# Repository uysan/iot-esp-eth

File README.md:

# ESP32 Ethernet, Wi-Fi & Serial Gateway

_Open Source Hardware Developed With Open Source Software_ [*](#development-software)

## Overview

<picture>
  <source media="(prefers-color-scheme: dark)" srcset="./pcb/3dviewb.png">
  <source media="(prefers-color-scheme: light)" srcset="./pcb/3dvieww.png">
  
</picture>

A hardware design which includes ESP32, Ethernet, Wi-Fi, USB and serial connectivity. **iot-esp-eth** is suitable to use as a gateway between Ethernet, Wi-Fi and serial. When used with [esp-at](https://github.com/espressif/esp-at) project, you can connect wired or wireless networks with AT commands sent to USB or serial ports. You may also operate it with custom firmware, since it is not different from a usual ESP32 development kit.

**iot-esp-eth** may be used as an attachment to a base board. Standalone usage with USB supply is possible as well.

ESP-IDF automatic bootloader activation is supported on USB port. This port is connected to UART0 of ESP32.

Schematic, PCB layout and antenna design are available in this repository. **iot-esp-eth** is compatible with many example projects at [espressif](https://github.com/espressif/) github repository.

## Table of Contents

- [PCB Design](./pcb/) : KiCAD project including schematic, layout, BOM, Gerber files.
- [Antenna Design](./antenna/) : OpenEMS project for PCB antenna design including simulation scripts, figures and prototype measurements.
- [Firmware](./firmware/) : espressif/esp-at project modified to include iot-esp-eth configuration.
- [Documents](./document/) : Project files for diagrams and documents.

## Pinout Diagram

## Block Diagram

## Datasheet

[UYS2101IA, UYS2101CA - ESP32 Ethernet, Wi-Fi & Serial Gateway](./document/uys2101.pdf)

## Features

- ESP32-D0WD-V3 Xtensa® Dual-core 32-bit LX6 240MHz MCU 
- 16 MB Serial Flash Memory
- 520 KB SRAM & 448 KB ROM
- 10/100 Mbit Ethernet (RTL8201F)
- Wi-Fi 802.11 b/g/n 2.4GHz
- Integrated 2.4GHz Antenna
- USB 2.0 Programming & Monitoring Interface
- 5V to 3.3V Voltage Regulator
- Supply Voltage Supervisor
- Built-in 40 MHz & 32.758 kHz MCU Crystals

## Development Software

This project was developed with open source tools including but not limited to KiCAD, OpenEMS, Octave, FreeCAD, Paraview, Inkscape and Scribus on a PC running Ubuntu Desktop edition.

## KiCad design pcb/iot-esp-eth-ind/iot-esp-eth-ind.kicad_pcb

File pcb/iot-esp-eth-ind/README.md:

# ESP32 Ethernet, Wi-Fi & Serial Gateway

_Open Source Hardware Developed With Open Source Software_ [*](#development-software)

## Overview

This directory contains KiCAD project files, generated PCB images, Gerber, panel configuration files, interactive HTML based assembly list, bill of materials and position (pick & place) data.

Components of the **iot-esp-eth-ind** board has an operating range of -40॰C to +85॰C. Board layout has 4-layers and is designed according to the JLCPCB impedance controlled stack up of [JLC04161H-7628](https://jlcpcb.com/impedance).

PCB panels can be automatically generated with KiKit (KiCAD plugin). Configuration files are in the related directory.

## Files

[Schematics](./iot-esp-eth-ind.pdf)

[PCB Layers](./iot-esp-eth-ind-layers.pdf)

[Bill of Materials](./iot-esp-eth-ind-bom.csv)

[Position Data](./iot-esp-eth-ind-all-pos.csv)

[Interactive assembly part list](./bom/ibom.html)

[Panel Configuration](./panel/config.json)

[Dimensions](./iot-esp-eth-ind-dimensions.pdf)

## Images

Copper layers:

Top view:

Bottom view:

## Development Software

This project was developed with open source tools including but not limited to KiCAD, OpenEMS, Octave, FreeCAD, Paraview, Inkscape and Scribus on a PC running Ubuntu Desktop edition.

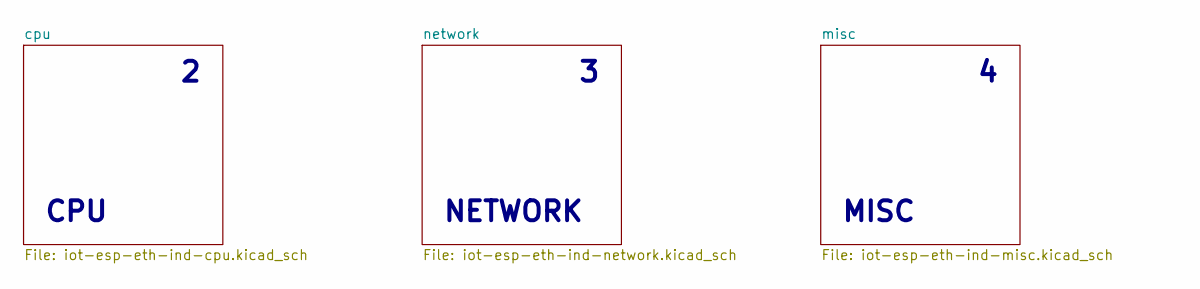
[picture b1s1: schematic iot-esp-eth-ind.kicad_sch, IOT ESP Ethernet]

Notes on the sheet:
NETWORK
MISC
CPU

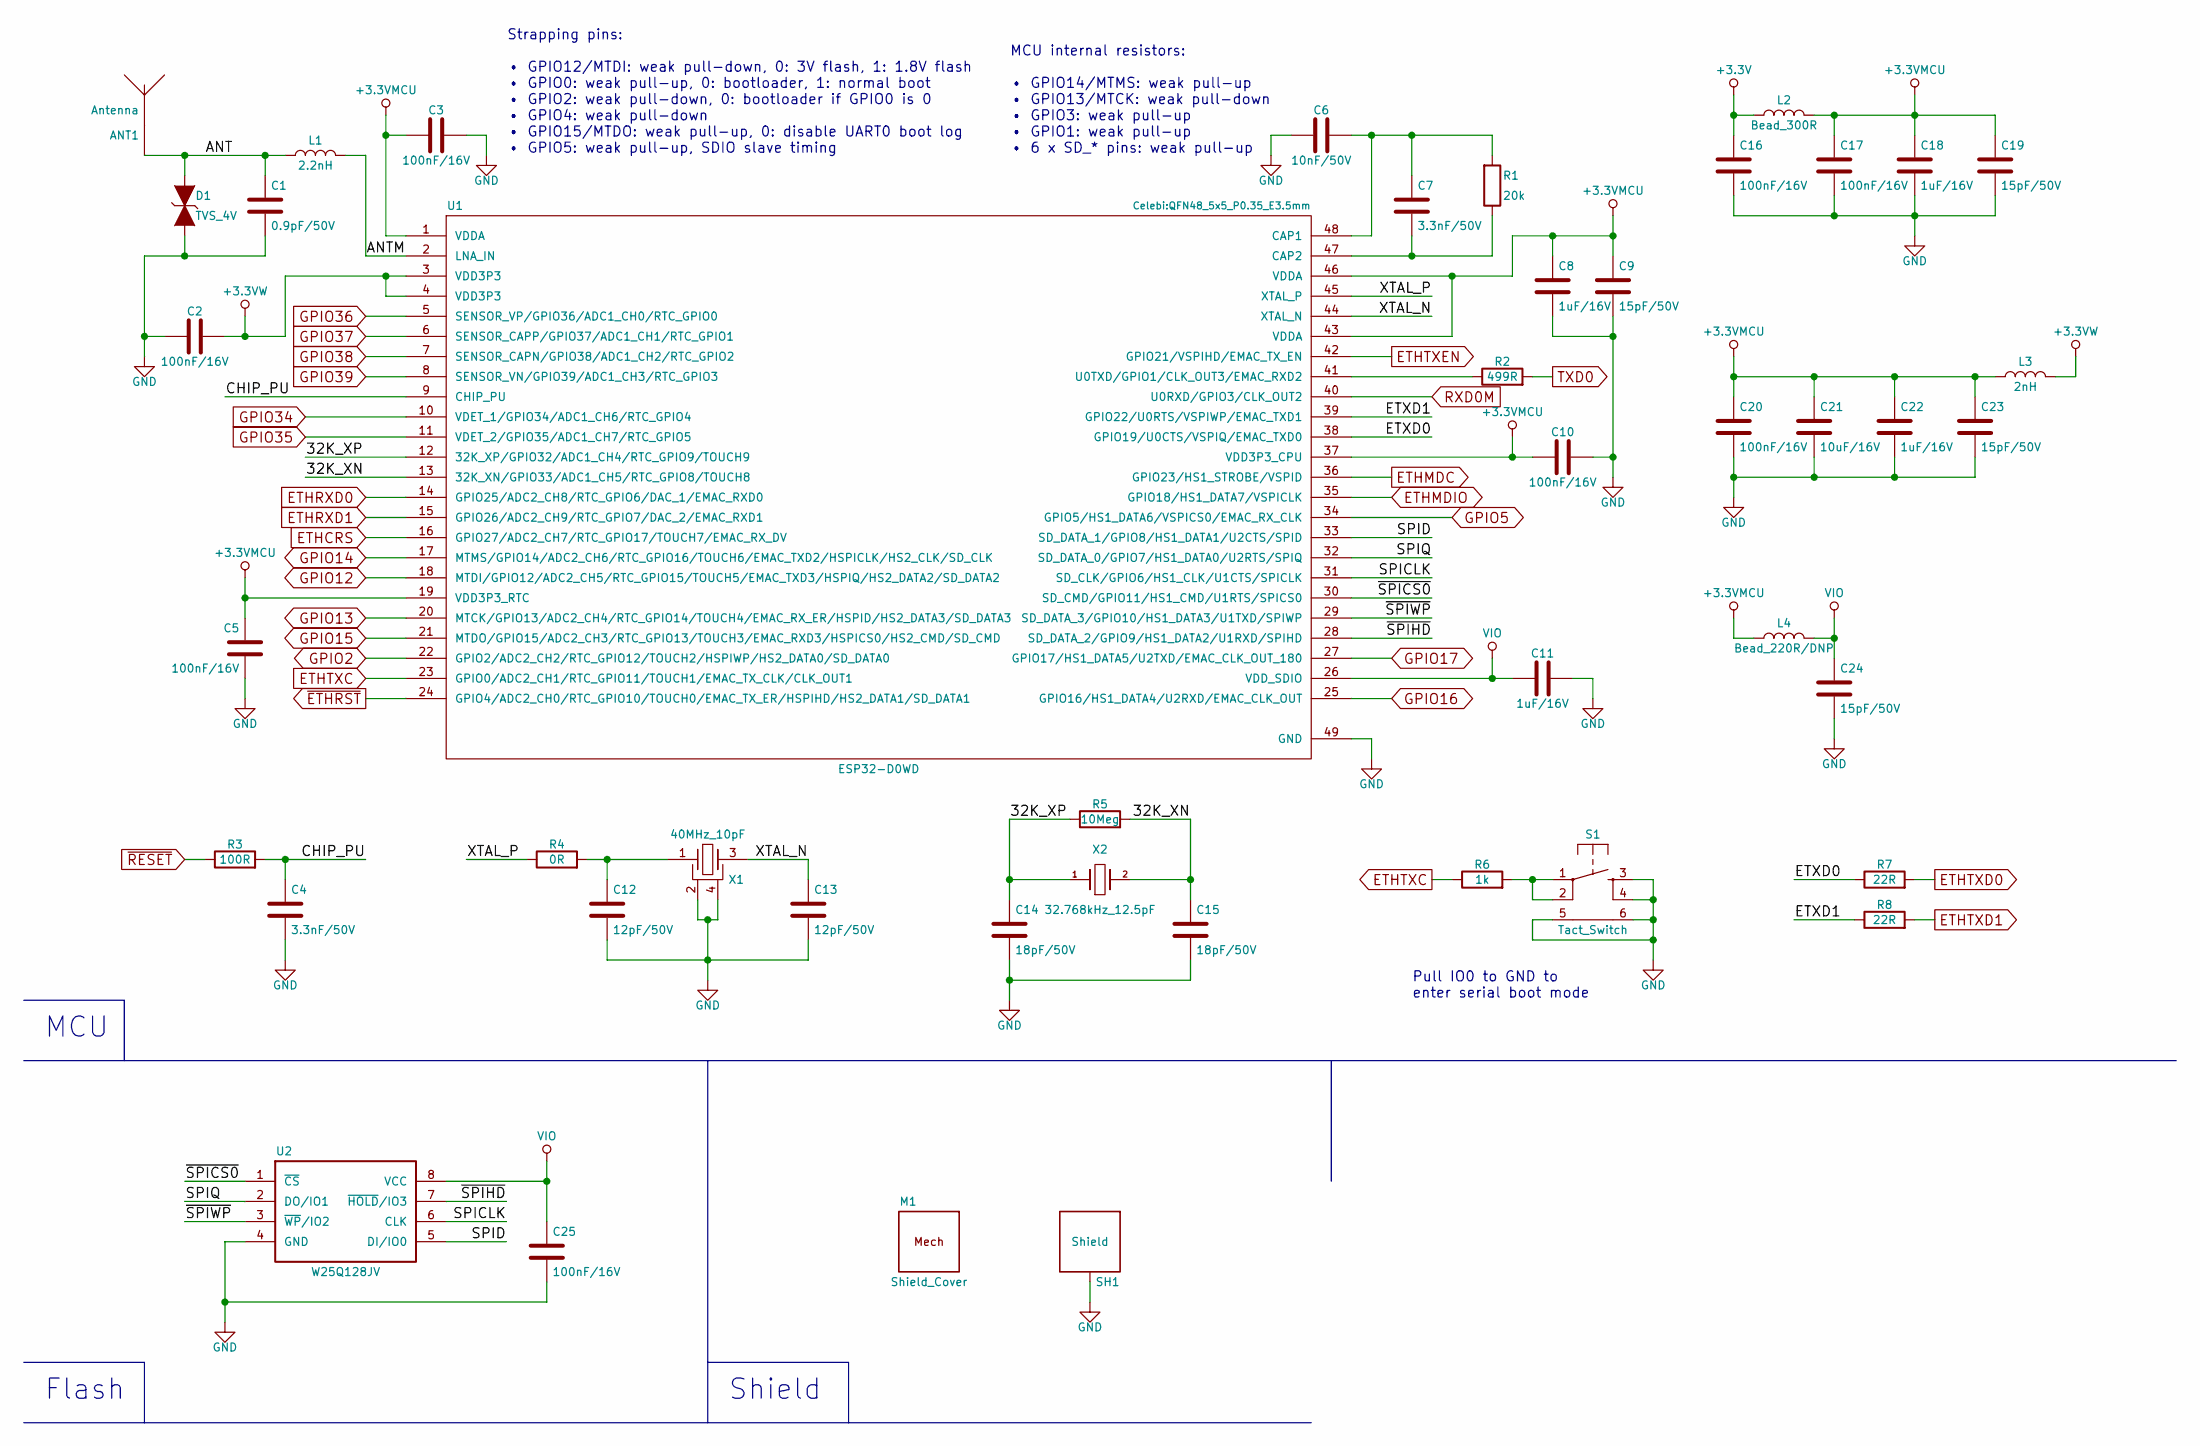
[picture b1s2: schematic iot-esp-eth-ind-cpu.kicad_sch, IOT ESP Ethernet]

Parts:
ANT1: Antenna; N.A.; Tolerance _; PartNumber _; Digikey _
C1: 0.9pF/50V; SM0402C; Tolerance 0.1pF; PartNumber 885392005022; Digikey !13-CC0402BRNPO9BNR90CT-ND
C2, C3, C5, C10, C16, C17, C20, C25: 100nF/16V; SM0402C; Tolerance 10%; PartNumber CL05B104KO5NNNC; Digikey 1276-1001-1-ND
C4, C7: 3.3nF/50V; SM0402C; Tolerance 10%; PartNumber CL05B332KB5NNNC; Digikey 1276-1552-1-ND
C6: 10nF/50V; SM0402C; Tolerance 10%; PartNumber CC0402KRX7R9BB103; Digikey 311-1349-1-ND
C8, C11, C18, C22: 1uF/16V; SM0603C; Tolerance 10%; PartNumber CC0603KRX7R7BB105; Digikey 311-1446-1-ND
C9, C19, C23, C24: 15pF/50V; SM0402C; Tolerance 5%; PartNumber CC0402JRNPO9BN150; Digikey 311-1017-1-ND
C12, C13: 12pF/50V; SM0402C; Tolerance 5%; PartNumber CC0402JRNPO9BN120; Digikey 311-1016-1-ND
C14, C15: 18pF/50V; SM0402C; Tolerance 5%; PartNumber CC0402JRNPO9BN180; Digikey 311-1415-1-ND
C21: 10uF/16V; SM0805C; Tolerance 10%; PartNumber CL21B106KOQNNNE; Digikey 1276-2872-1-ND
D1: TVS_4V; SM0402V; Tolerance _; PartNumber LXES15AAA1-153; Digikey 490-13210-2-ND
L1: 2.2nH; SM0402L; Tolerance 0.1nH; PartNumber 7447840022G; Digikey 732-7447840022GCT-ND
L2: Bead_300R; SM0603L; Tolerance 25%; PartNumber 742792641; Digikey 732-1592-1-ND
L3: 2nH; SM0402L; Tolerance 0.2nH; PartNumber 744765020A; Digikey 732-1705-1-ND
L4: Bead_220R/DNP; SM0402L; Tolerance 25%; PartNumber 742792780; Digikey 732-1569-1-ND
M1: Shield_Cover; N.A.; Tolerance _; PartNumber 36003160S; Digikey 732-11644-1-ND
R1: 20k; SM0402; Tolerance 1%; PartNumber RC0402FR-0720KL; Digikey 311-20.0KLRCT-ND
R2: 499R; SM0402; Tolerance 1%; PartNumber RC0402FR-07499RL; Digikey 311-499LRCT-ND
R3: 100R; SM0402; Tolerance 1%; PartNumber RC0402FR-07100RL; Digikey 311-100LRCT-ND
R4: 0R; SM0402; Tolerance Jumper; PartNumber RC0402JR-070RL; Digikey 311-0.0JRCT-ND
R5: 10Meg; SM0402; Tolerance 1%; PartNumber RC0402FR-0710ML; Digikey 311-10.0MLRCT-ND
R6: 1k; SM0402; Tolerance 1%; PartNumber RC0402FR-071KL; Digikey 311-1.00KLRCT-ND
R7, R8: 22R; SM0402; Tolerance 1%; PartNumber RC0402FR-0722RL; Digikey 311-22.0LRCT-ND
S1: Tact_Switch; switch-WE-WS-TASV-3x2.6_H1.4mm; Tolerance _; PartNumber 435171014816; Digikey 732-435171014816CT-ND
SH1: Shield; shield-36103166S; Tolerance _; PartNumber 36103166S; Digikey 732-11652-1-ND
U1: ESP32-D0WD; QFN48_5x5_P0.35_E3.5mm; Tolerance _; PartNumber ESP32-D0WD-V3; Digikey 1904-ESP32-D0WD-V3CT-ND
U2: W25Q128JV; SO8_5.2x5.2_P1.27mm; Tolerance _; PartNumber W25Q128JVSIQ; Digikey W25Q128JVSIQ-ND
X1: 40MHz_10pF; xtal-2.5x2.0mm_4pin; Tolerance 10ppm; PartNumber R2520-40.000-10-F-1010-EXT-TR; Digikey 2151-R2520-40.000-10-F-1010-EXT-TRCT-ND
X2: 32.768kHz_12.5pF; xtal-3.2x1.5mm; Tolerance 10ppm; PartNumber RT3215-32.768-12.5-TR-10PPM; Digikey 2151-RT3215-32.768-12.5-TR-10PPMCT-ND

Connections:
+3.3V: C16.1, L2.1; also elsewhere on the board
+3.3VMCU: C3.2, C5.1, C8.1, C9.1, C10.2, C17.1, C18.1, C19.1, C20.1, C21.1, C22.1, C23.1, L2.2, L3.1, L4.1, U1.1 (VDDA), U1.19 (VDD3P3_RTC), U1.37 (VDD3P3_CPU), U1.43 (VDDA), U1.46 (VDDA)
+3.3VW: C2.1, L3.2, U1.3 (VDD3P3), U1.4 (VDD3P3)
/cpu/32K_XN: C15.1, R5.2, U1.13 (32K_XN/GPIO33/ADC1_CH5/RTC_GPIO8/TOUCH8), X2.2 (B)
/cpu/32K_XP: C14.1, R5.1, U1.12 (32K_XP/GPIO32/ADC1_CH4/RTC_GPIO9/TOUCH9), X2.1 (A)
/cpu/ANT: ANT1.1, C1.1, D1.2 (A), L1.1
/cpu/ANTM: L1.2, U1.2 (LNA_IN)
/cpu/CHIP_PU: C4.1, R3.2, U1.9 (CHIP_PU)
/cpu/ETXD0: R7.1, U1.38 (GPIO19/U0CTS/VSPIQ/EMAC_TXD0)
/cpu/ETXD1: R8.1, U1.39 (GPIO22/U0RTS/VSPIWP/EMAC_TXD1)
/cpu/SPICLK: U1.31 (SD_CLK/GPIO6/HS1_CLK/U1CTS/SPICLK), U2.6 (CLK)
/cpu/SPID: U1.33 (SD_DATA_1/GPIO8/HS1_DATA1/U2CTS/SPID), U2.5 (DI/IO0)
/cpu/SPIQ: U1.32 (SD_DATA_0/GPIO7/HS1_DATA0/U2RTS/SPIQ), U2.2 (DO/IO1)
/cpu/XTAL_N: C13.1, U1.44 (XTAL_N), X1.3 (B)
/cpu/XTAL_P: R4.1, U1.45 (XTAL_P)
/cpu/~SPICS0: U1.30 (SD_CMD/GPIO11/HS1_CMD/U1RTS/SPICS0), U2.1 (~CS)
/cpu/~SPIHD: U1.28 (SD_DATA_2/GPIO9/HS1_DATA2/U1RXD/SPIHD), U2.7 (~HOLD/IO3)
/cpu/~SPIWP: U1.29 (SD_DATA_3/GPIO10/HS1_DATA3/U1TXD/SPIWP), U2.3 (~WP/IO2)
ETHCRS: U1.16 (GPIO27/ADC2_CH7/RTC_GPIO17/TOUCH7/EMAC_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); also elsewhere on the board
ETHMDC: U1.36 (GPIO23/HS1_STROBE/VSPID); also elsewhere on the board
ETHMDIO: U1.35 (GPIO18/HS1_DATA7/VSPICLK); also elsewhere on the board
ETHRXD0: U1.14 (GPIO25/ADC2_CH8/RTC_GPIO6/DAC_1/EMAC_RX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); also elsewhere on the board
ETHRXD1: U1.15 (GPIO26/ADC2_CH9/RTC_GPIO7/DAC_2/EMAC_RX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); also elsewhere on the board
ETHTXC: R6.1, U1.23 (GPIO0/ADC2_CH1/RTC_GPIO11/TOUCH1/EMAC_T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); also elsewhere on the board
ETHTXD0: R7.2; also elsewhere on the board
ETHTXD1: R8.2; also elsewhere on the board
ETHTXEN: U1.42 (GPIO21/VSPIHD/EMAC_TX_EN); also elsewhere on the board
GND: C1.2, C2.2, C3.1, C4.2, C5.2, C6.1, C8.2, C9.2, C10.1, C11.2, C12.2, C13.2, C14.2, C15.2, C16.2, C17.2, C18.2, C19.2, C20.2, C21.2, C22.2, C23.2, C24.2, C25.2, D1.1 (A), S1.3, S1.4, S1.5, S1.6, SH1.1 (GND), U1.49 (GND), U2.4 (GND), X1.2 (GND), X1.4 (GND); also elsewhere on the board
GPIO2: U1.22 (GPIO2/ADC2_CH2/RTC_GPIO12/TOUCH2/HSPIWP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); also elsewhere on the board
GPIO5: U1.34 (GPIO5/HS1_DATA6/VSPICS0/EMAC_RX_CLK); also elsewhere on the board
GPIO12: U1.18 (MTDI/GPIO12/ADC2_CH5/RTC_GPIO15/TOUCH5/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); also elsewhere on the board
GPIO13: U1.20 (MTCK/GPIO13/ADC2_CH4/RTC_GPIO14/TOUCH4/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); also elsewhere on the board
GPIO14: U1.17 (MTMS/GPIO14/ADC2_CH6/RTC_GPIO16/TOUCH6/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); also elsewhere on the board
GPIO15: U1.21 (MTDO/GPIO15/ADC2_CH3/RTC_GPIO13/TOUCH3/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); also elsewhere on the board
GPIO16: U1.25 (GPIO16/HS1_DATA4/U2RXD/EMAC_CLK_OUT); also elsewhere on the board
GPIO17: U1.27 (GPIO17/HS1_DATA5/U2TXD/EMAC_CLK_OUT_180); also elsewhere on the board
GPIO34: U1.10 (VDET_1/GPIO34/ADC1_CH6/RTC_GPIO4); also elsewhere on the board
GPIO35: U1.11 (VDET_2/GPIO35/ADC1_CH7/RTC_GPIO5); also elsewhere on the board
GPIO36: U1.5 (SENSOR_VP/GPIO36/ADC1_CH0/RTC_GPIO0); also elsewhere on the board
GPIO37: U1.6 (SENSOR_CAPP/GPIO37/ADC1_CH1/RTC_GPIO1); also elsewhere on the board
GPIO38: U1.7 (SENSOR_CAPN/GPIO38/ADC1_CH2/RTC_GPIO2); also elsewhere on the board
GPIO39: U1.8 (SENSOR_VN/GPIO39/ADC1_CH3/RTC_GPIO3); also elsewhere on the board
unnamed: C6.2, C7.1, R1.2, U1.48 (CAP1)
unnamed: C7.2, R1.1, U1.47 (CAP2)
unnamed: C12.1, R4.2, X1.1 (A)
unnamed: R2.1, U1.41 (U0TXD/GPIO1/CLK_OUT3/EMAC_RXD2)
unnamed: R6.2, S1.1, S1.2
RXD0M: U1.40 (U0RXD/GPIO3/CLK_OUT2); also elsewhere on the board
TXD0: R2.2; also elsewhere on the board
VIO: C11.1, C24.1, C25.1, L4.2, U1.26 (VDD_SDIO), U2.8 (VCC)
~ETHRST: U1.24 (GPIO4/ADC2_CH0/RTC_GPIO10/TOUCH0/EMAC_T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); also elsewhere on the board
~RESET: R3.1; also elsewhere on the board

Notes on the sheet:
MCU internal resistors: • GPIO14/MTMS: weak pull-up • GPIO13/MTCK: weak pull-down • GPIO3: weak pull-up • GPIO1: weak pull-up • 6 x SD_* pins: weak pull-up
Shield
Flash
MCU
Strapping pins: • GPIO12/MTDI: weak pull-down, 0: 3V flash, 1: 1.8V flash • GPIO0: weak pull-up, 0: bootloader, 1: normal boot • GPIO2: weak pull-down, 0: bootloader if GPIO0 is 0 • GPIO4: weak pull-down • GPIO15/MTDO: weak pull-up, 0: disable UART0 boot log • GPIO5: weak pull-up, SDIO slave timing
Pull IO0 to GND to enter serial boot mode

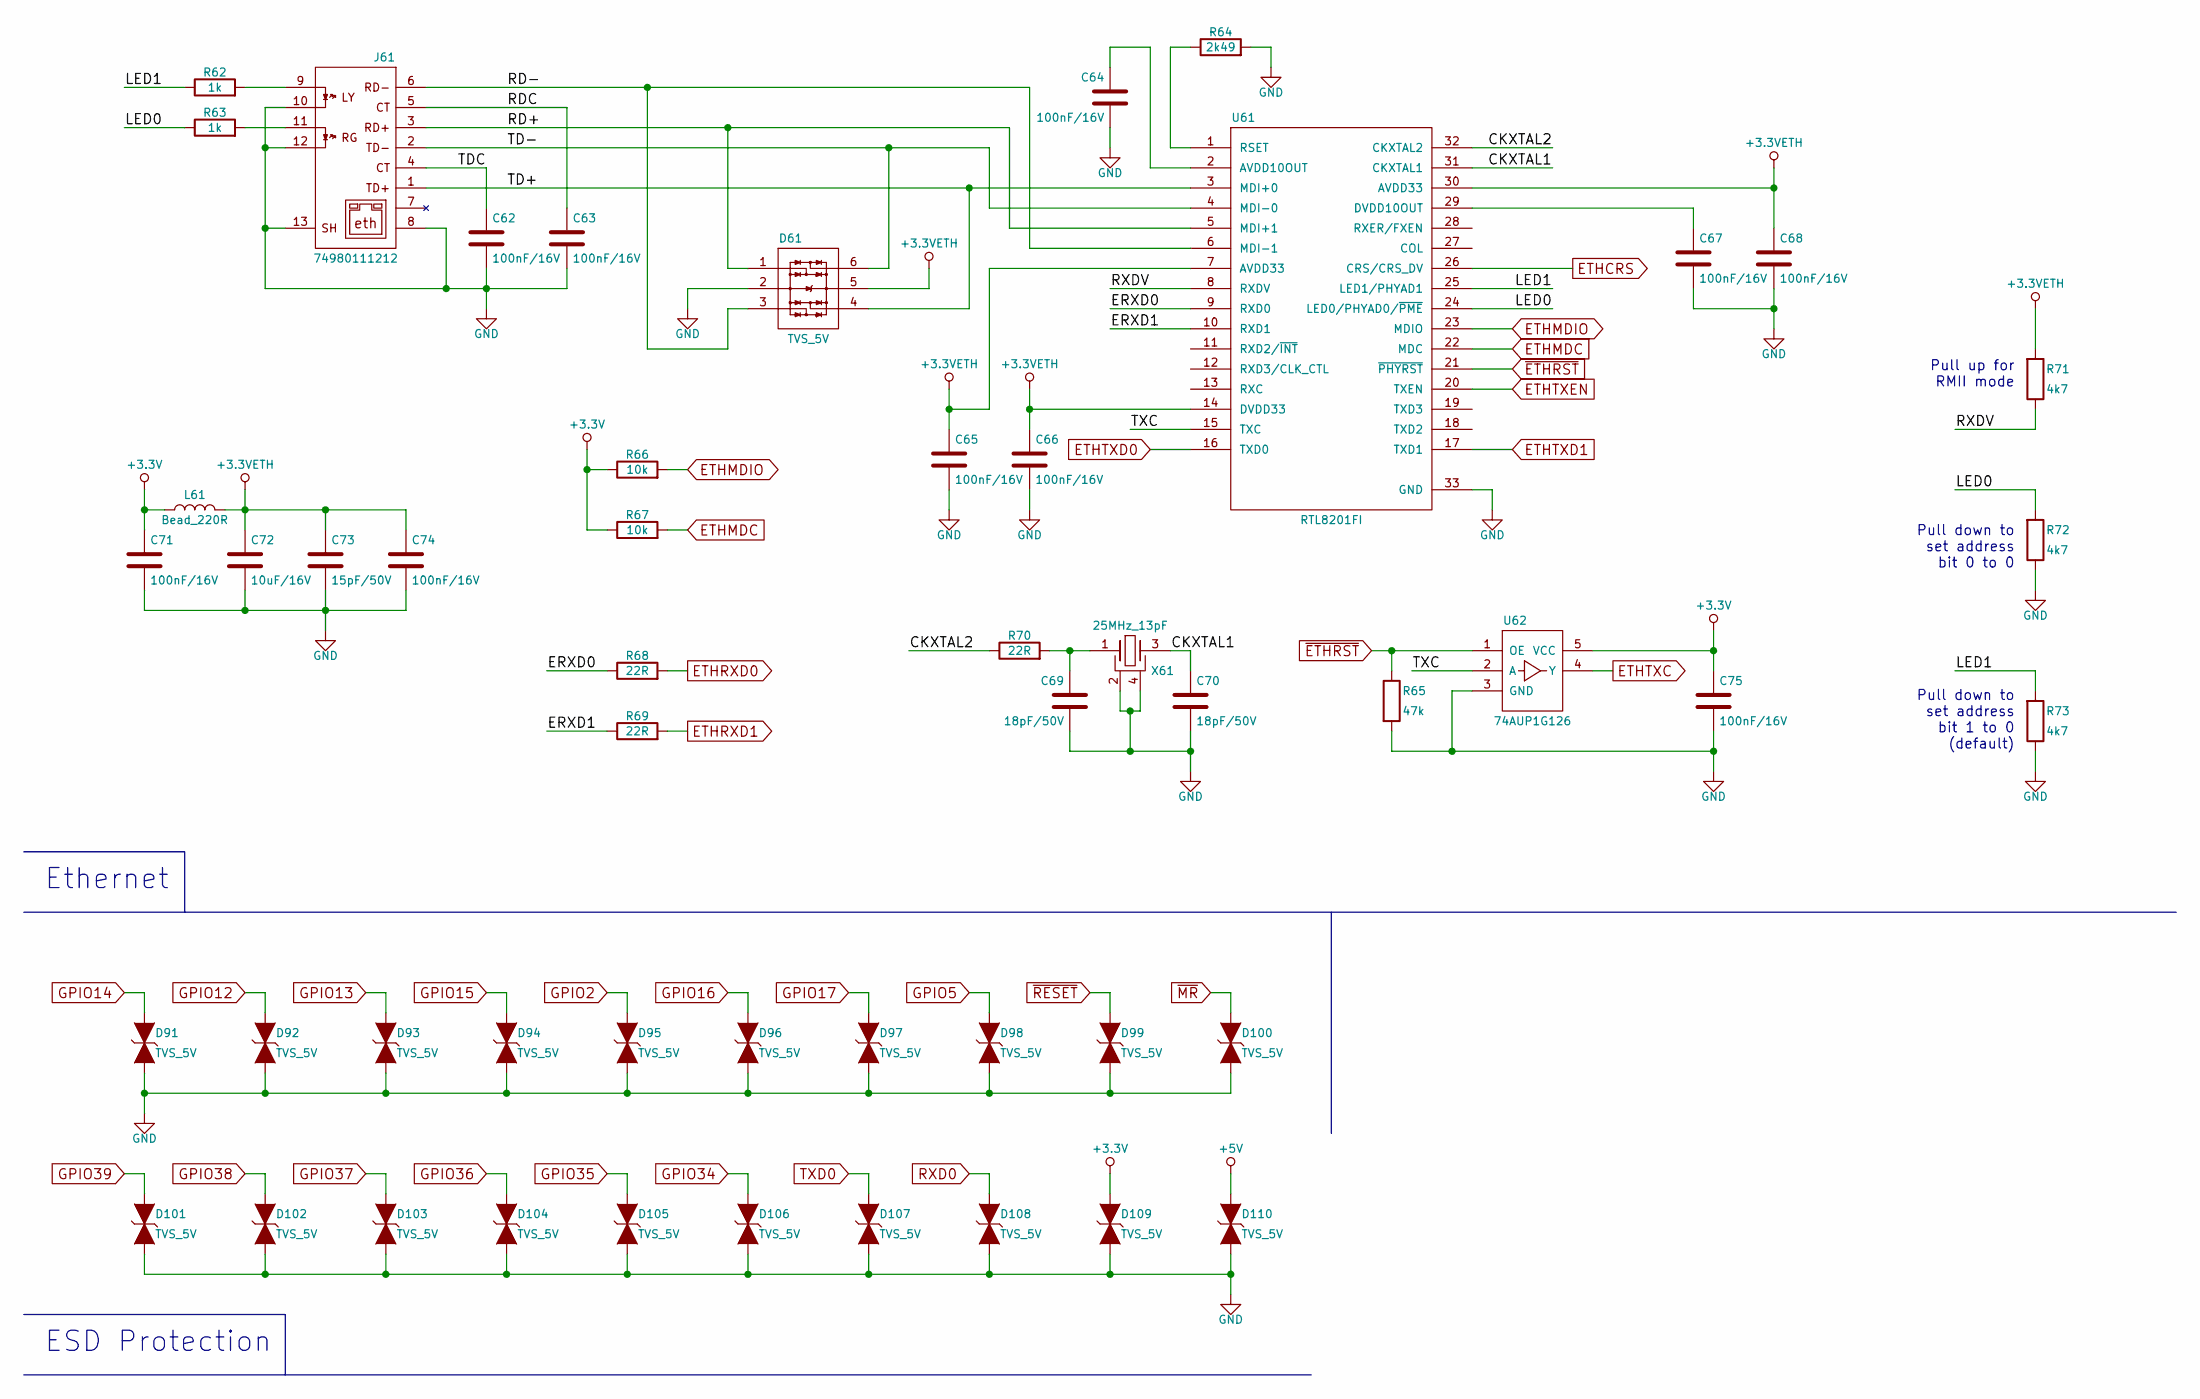
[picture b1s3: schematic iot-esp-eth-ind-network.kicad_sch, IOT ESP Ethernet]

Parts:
C62, C63, C64, C65, C66, C67, C68, C71, C74, C75: 100nF/16V; SM0402C; Tolerance 10%; PartNumber CL05B104KO5NNNC; Digikey 1276-1001-1-ND
C69, C70: 18pF/50V; SM0402C; Tolerance 5%; PartNumber CC0402JRNPO9BN180; Digikey 311-1415-1-ND
C72: 10uF/16V; SM0805C; Tolerance 10%; PartNumber CL21B106KOQNNNE; Digikey 1276-2872-1-ND
C73: 15pF/50V; SM0402C; Tolerance 5%; PartNumber CC0402JRNPO9BN150; Digikey 311-1017-1-ND
D61: TVS_5V; SOT23-6L; Tolerance _; PartNumber 824015; Digikey 732-4467-1-ND
D91, D92, D93, D94, D95, D96, D97, D98, D99, D100, D101, D102, D103, D104, D105, D106, D107, D108, D109, D110: TVS_5V; DFN1006-2; Tolerance _; PartNumber ULC0511CDN; Digikey !490-12804-1-ND
J61: 74980111212; eth-74980111212; Tolerance _; PartNumber 74980111212; Digikey _
L61: Bead_220R; SM0402L; Tolerance 25%; PartNumber 742792780; Digikey 732-1569-1-ND
R62, R63: 1k; SM0402; Tolerance 1%; PartNumber RC0402FR-071KL; Digikey 311-1.00KLRCT-ND
R64: 2k49; SM0402; Tolerance 1%; PartNumber RC0402FR-072K49L; Digikey 311-2.49KLRCT-ND
R65: 47k; SM0402; Tolerance 1%; PartNumber RC0402FR-0747KL; Digikey 311-47.0KLRCT-ND
R66, R67: 10k; SM0402; Tolerance 1%; PartNumber RC0402FR-0710KL; Digikey 311-10.0KLRCT-ND
R68, R69, R70: 22R; SM0402; Tolerance 1%; PartNumber RC0402FR-0722RL; Digikey 311-22.0LRCT-ND
R71, R72, R73: 4k7; SM0402; Tolerance 1%; PartNumber RC0402FR-074K7L; Digikey 311-4.7KLRCT-ND
U61: RTL8201FI; QFN32_5x5_P0.5_E3.35mm; Tolerance _; PartNumber RTL8201FI-VC-CG; Digikey _
U62: 74AUP1G126; SOT23-5L; Tolerance _; PartNumber SN74AUP1G126DBVR; Digikey 296-18005-1-ND
X61: 25MHz_13pF; xtal-3.2x2.5mm_4pin; Tolerance 7ppm; PartNumber RH100-25.000-13-F-0715-EXT-TR-NS1; Digikey 2151-RH100-25.000-13-F-0715-EXT-TR-NS1C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

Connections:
+3.3V: C71.1, C75.1, D109.2 (A), L61.1, R66.1, R67.1, U62.5 (VCC); also elsewhere on the board
+3.3VETH: C65.1, C66.1, C68.1, C72.1, C73.1, C74.1, D61.5 (VDD), L61.2, R71.2, U61.7 (AVDD33), U61.14 (DVDD33), U61.30 (AVDD33)
+5V: D110.2 (A); also elsewhere on the board
/network/CKXTAL1: C70.1, U61.31 (CKXTAL1), X61.3 (B)
/network/CKXTAL2: R70.1, U61.32 (CKXTAL2)
/network/ERXD0: R68.1, U61.9 (RXD0)
/network/ERXD1: R69.1, U61.10 (RXD1)
/network/LED0: R63.1, R72.2, U61.24 (LED0/PHYAD0/~PME)
/network/LED1: R62.1, R73.2, U61.25 (LED1/PHYAD1)
/network/RD+: D61.1 (IO1), J61.3 (RD+), U61.5 (MDI+1)
/network/RD-: D61.3 (IO2), J61.6 (RD-), U61.6 (MDI-1)
/network/RDC: C63.1, J61.5 (CT)
/network/RXDV: R71.1, U61.8 (RXDV)
/network/TD+: D61.4 (IO3), J61.1 (TD+), U61.3 (MDI+0)
/network/TD-: D61.6 (IO4), J61.2 (TD-), U61.4 (MDI-0)
/network/TDC: C62.1, J61.4 (CT)
/network/TXC: U61.15 (TXC), U62.2 (A)
ETHCRS: U61.26 (CRS/CRS_DV); also elsewhere on the board
ETHMDC: R67.2, U61.22 (MDC); also elsewhere on the board
ETHMDIO: R66.2, U61.23 (MDIO); also elsewhere on the board
ETHRXD0: R68.2; also elsewhere on the board
ETHRXD1: R69.2; also elsewhere on the board
ETHTXC: U62.4 (Y); also elsewhere on the board
ETHTXD0: U61.16 (TXD0); also elsewhere on the board
ETHTXD1: U61.17 (TXD1); also elsewhere on the board
ETHTXEN: U61.20 (TXEN); also elsewhere on the board
GND: C62.2, C63.2, C64.2, C65.2, C66.2, C67.2, C68.2, C69.2, C70.2, C71.2, C72.2, C73.2, C74.2, C75.2, D61.2 (GND), D91.1 (A), D92.1 (A), D93.1 (A), D94.1 (A), D95.1 (A), D96.1 (A), D97.1 (A), D98.1 (A), D99.1 (A), D100.1 (A), D101.1 (A), D102.1 (A), D103.1 (A), D104.1 (A), D105.1 (A), D106.1 (A), D107.1 (A), D108.1 (A), D109.1 (A), D110.1 (A), J61.8 (GND), J61.10 (LED1-), J61.12 (LED2+), J61.13 (SHIELD), R64.2, R65.2, R72.1, R73.1, U61.33 (GND), U62.3 (GND), X61.2 (GND), X61.4 (GND); also elsewhere on the board
GPIO2: D95.2 (A); also elsewhere on the board
GPIO5: D98.2 (A); also elsewhere on the board
GPIO12: D92.2 (A); also elsewhere on the board
GPIO13: D93.2 (A); also elsewhere on the board
GPIO14: D91.2 (A); also elsewhere on the board
GPIO15: D94.2 (A); also elsewhere on the board
GPIO16: D96.2 (A); also elsewhere on the board
GPIO17: D97.2 (A); also elsewhere on the board
GPIO34: D106.2 (A); also elsewhere on the board
GPIO35: D105.2 (A); also elsewhere on the board
GPIO36: D104.2 (A); also elsewhere on the board
GPIO37: D103.2 (A); also elsewhere on the board
GPIO38: D102.2 (A); also elsewhere on the board
GPIO39: D101.2 (A); also elsewhere on the board
unnamed: C64.1, U61.2 (AVDD10OUT)
unnamed: C67.1, U61.29 (DVDD10OUT)
unnamed: C69.1, R70.2, X61.1 (A)
unnamed: J61.9 (LED1+), R62.2
unnamed: J61.11 (LED2-), R63.2
unnamed: R64.1, U61.1 (RSET)
RXD0: D108.2 (A); also elsewhere on the board
TXD0: D107.2 (A); also elsewhere on the board
~ETHRST: R65.1, U61.21 (~PHYRST), U62.1 (OE); also elsewhere on the board
~MR: D100.2 (A); also elsewhere on the board
~RESET: D99.2 (A); also elsewhere on the board

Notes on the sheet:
ESD Protection
Pull down to set address bit 0 to 0
Pull down to set address bit 1 to 0 (default)
Pull up for RMII mode
Ethernet

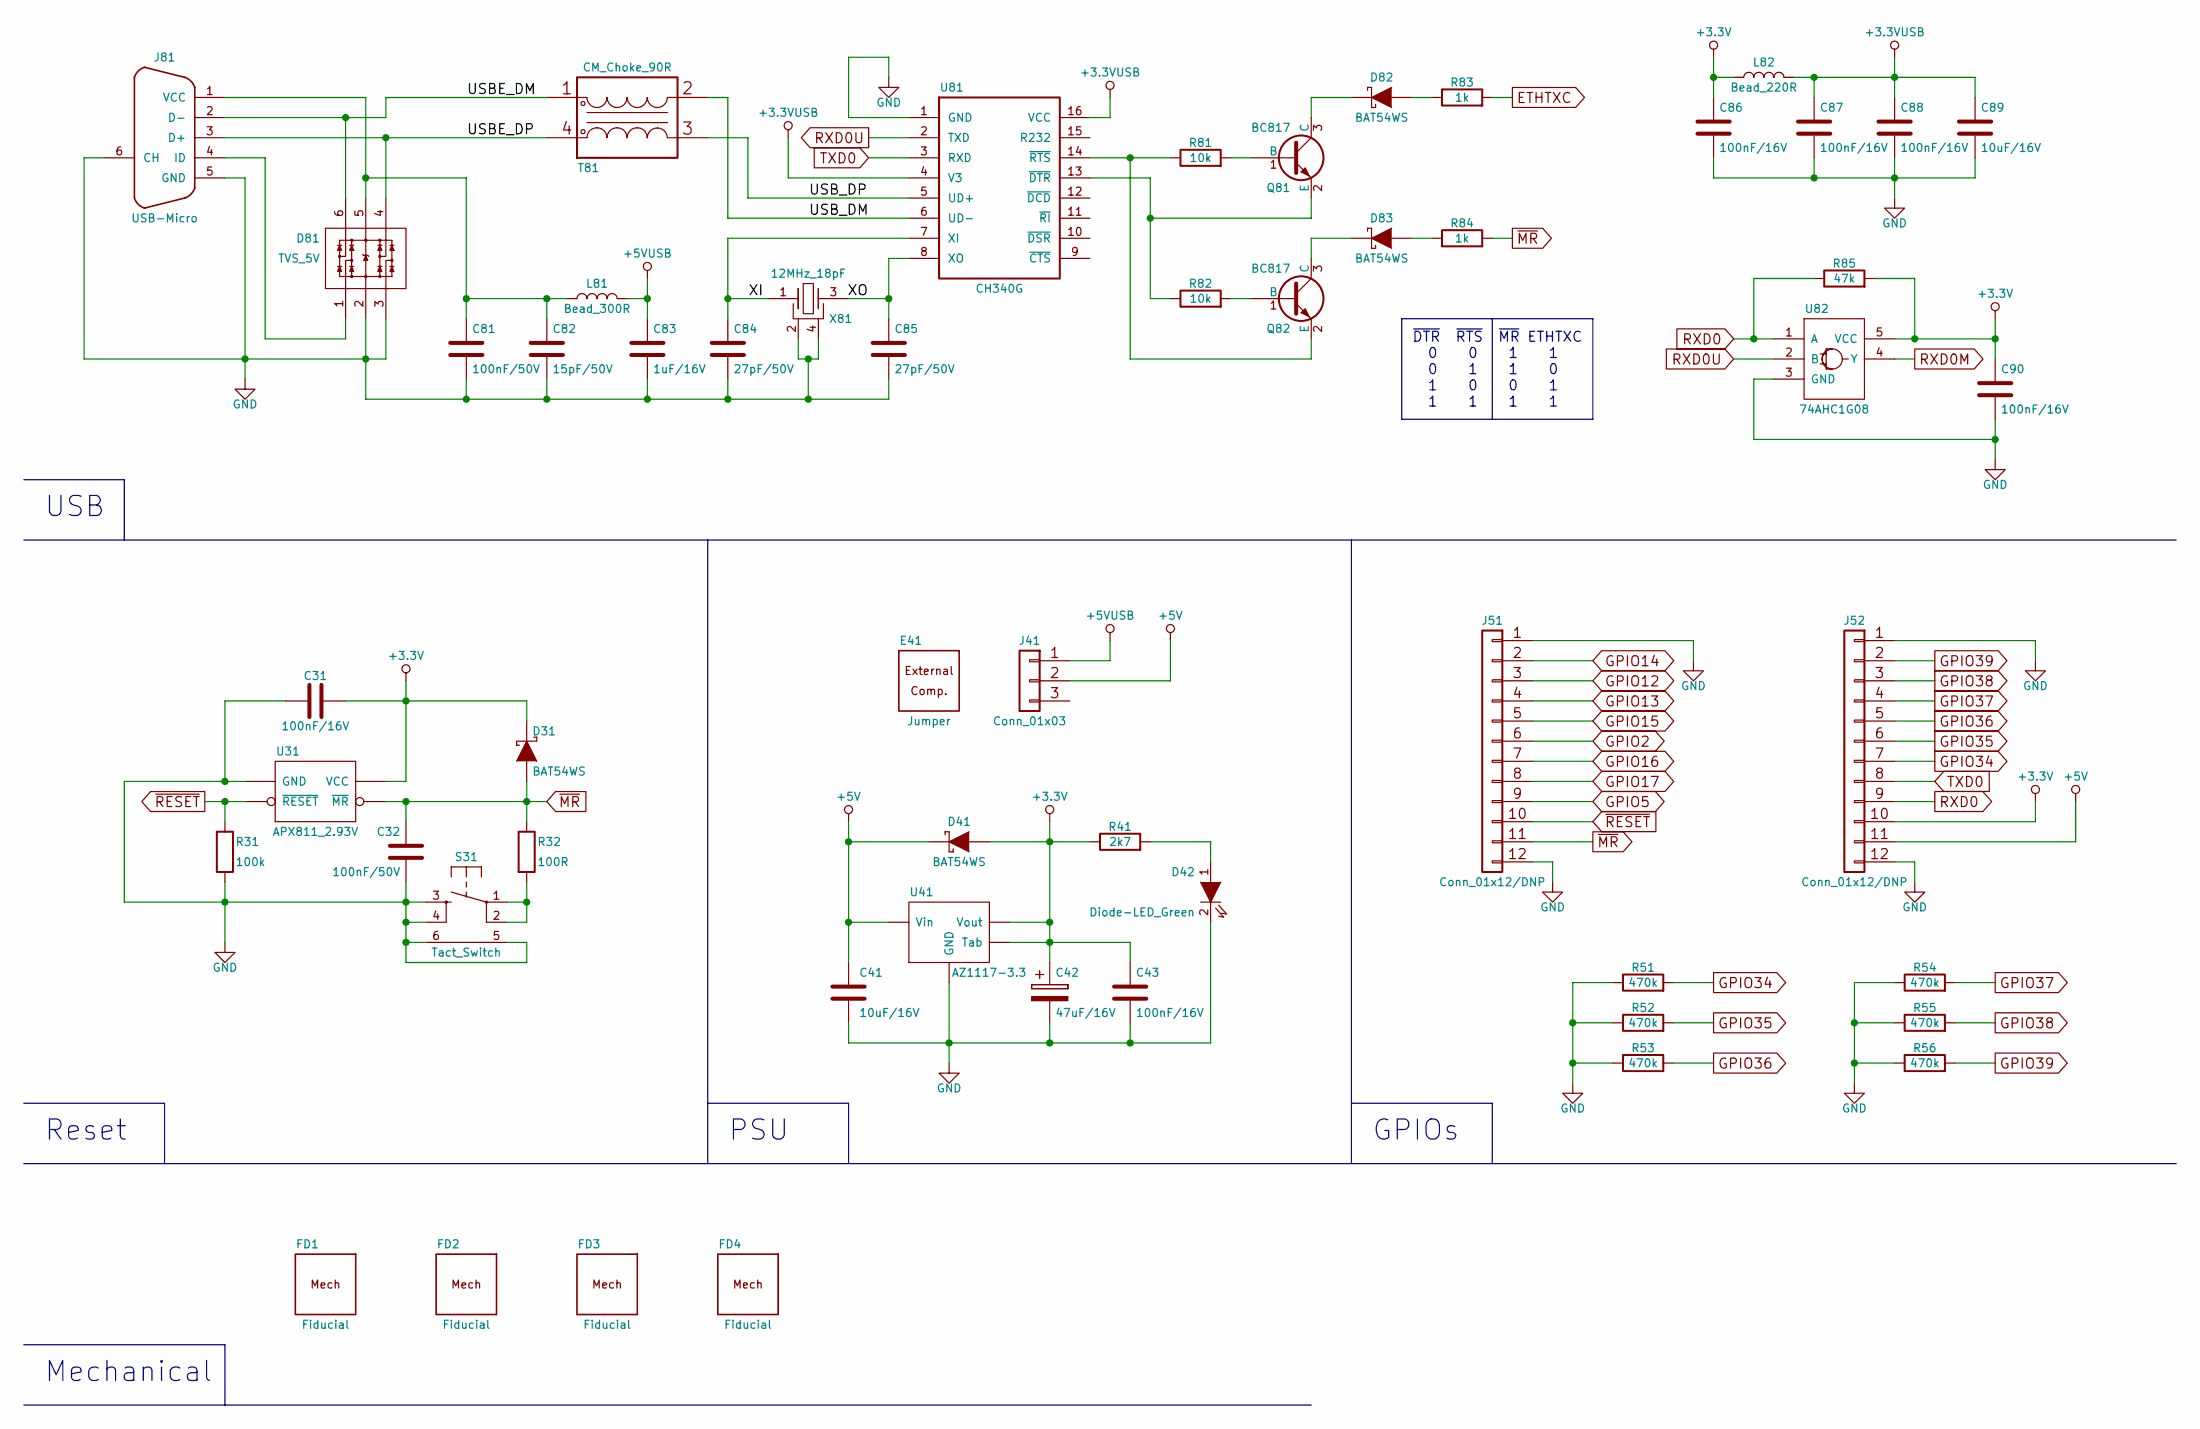
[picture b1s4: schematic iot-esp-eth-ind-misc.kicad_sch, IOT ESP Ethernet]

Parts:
C31, C43, C86, C87, C88, C90: 100nF/16V; SM0402C; Tolerance 10%; PartNumber CL05B104KO5NNNC; Digikey 1276-1001-1-ND
C32: 100nF/50V; SM0603C; Tolerance 10%; PartNumber CL10B104KB8NNNC; Digikey 1276-1000-1-ND
C41, C89: 10uF/16V; SM0805C; Tolerance 10%; PartNumber CL21B106KOQNNNE; Digikey 1276-2872-1-ND
C42: 47uF/16V; SMD-C-6032; Tolerance 10%; PartNumber TAJC476K016RNJ; Digikey 478-1718-1-ND
C81: 100nF/50V; SM0402C; Tolerance 10%; PartNumber CC0402KRX7R9BB104; Digikey 311-3566-1-ND
C82: 15pF/50V; SM0402C; Tolerance 5%; PartNumber CC0402JRNPO9BN150; Digikey 311-1017-1-ND
C83: 1uF/16V; SM0603C; Tolerance 10%; PartNumber CC0603KRX7R7BB105; Digikey 311-1446-1-ND
C84, C85: 27pF/50V; SM0402C; Tolerance 5%; PartNumber CC0402JRNPO9BN270; Digikey 311-1019-1-ND
D31, D41, D82, D83: BAT54WS; SOD323; Tolerance _; PartNumber BAT54WS_R1_00001; Digikey 3757-BAT54WS_R1_00001CT-ND
D42: Diode-LED_Green; led-SM0603_Green; Tolerance _; PartNumber LTST-C191KGKT; Digikey 160-1446-1-ND
D81: TVS_5V; SOT23-6L; Tolerance _; PartNumber 824015; Digikey 732-4467-1-ND
E41: Jumper; N.A.; Tolerance _; PartNumber X1301-B1NIB; Digikey !S9345-ND
FD1, FD2, FD3, FD4: Fiducial; fiducial_sc_D1_M3mm; Tolerance _; PartNumber _; Digikey _
J41: Conn_01x03; sil-1.27mm-3P; Tolerance _; PartNumber X1311WV-03J-C18D27; Digikey !SAM10238-ND
J51, J52: Conn_01x12/DNP; sil-12P; Tolerance _; PartNumber X6511WV-12H-C60D30; Digikey !S1012EC-12-ND
J81: USB-Micro; usb-629105136821; Tolerance _; PartNumber 629105136821; Digikey 732-3155-1-ND
L81: Bead_300R; SM0603L; Tolerance 25%; PartNumber 742792641; Digikey 732-1592-1-ND
L82: Bead_220R; SM0402L; Tolerance 25%; PartNumber 742792780; Digikey 732-1569-1-ND
Q81, Q82: BC817; SOT23-3; Tolerance _; PartNumber BC817-40-215; Digikey 1727-2919-1-ND
R31: 100k; SM0402; Tolerance 1%; PartNumber RC0402FR-07100KL; Digikey 311-100KLRCT-ND
R32: 100R; SM0402; Tolerance 1%; PartNumber RC0402FR-07100RL; Digikey 311-100LRCT-ND
R41: 2k7; SM0402; Tolerance 1%; PartNumber RC0402FR-072K7L; Digikey 311-2.70KLRCT-ND
R51, R52, R53, R54, R55, R56: 470k; SM0402; Tolerance 1%; PartNumber RC0402FR-07470KL; Digikey 311-470KLRCT-ND
R81, R82: 10k; SM0402; Tolerance 1%; PartNumber RC0402FR-0710KL; Digikey 311-10.0KLRCT-ND
R83, R84: 1k; SM0402; Tolerance 1%; PartNumber RC0402FR-071KL; Digikey 311-1.00KLRCT-ND
R85: 47k; SM0402; Tolerance 1%; PartNumber RC0402FR-0747KL; Digikey 311-47.0KLRCT-ND
S31: Tact_Switch; switch-WE-WS-TASV-3x2.6_H1.4mm; Tolerance _; PartNumber 435171014816; Digikey 732-435171014816CT-ND
T81: CM_Choke_90R; tr-smd-WE-CNSW_0805; Tolerance _; PartNumber 744231091; Digikey 732-3198-1-ND
U31: APX811_2.93V; SOT143-4; Tolerance 2%; PartNumber APX811-29UG-7; Digikey APX811-29UG-7DICT-ND
U41: AZ1117-3.3; SOT223; Tolerance 1%; PartNumber AZ1117IH-3.3TRG1; Digikey AZ1117IH-3.3TRG1DICT-ND
U81: CH340G; SO16_4x10.5_P1.27mm; Tolerance _; PartNumber CH340G; Digikey _
U82: 74AHC1G08; SOT23-5L; Tolerance _; PartNumber SN74AHC1G08DBVR; Digikey 296-1091-1-ND
X81: 12MHz_18pF; xtal-3.2x2.5mm_4pin; Tolerance 20ppm; PartNumber RH100-12.000-18-2020-EXT-TR; Digikey 2151-RH100-12.000-18-2020-EXT-TRCT-ND

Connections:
+3.3V: C31.1, C42.1, C43.1, C86.1, C90.1, D31.2 (K), D41.1 (A), J52.10, L82.1, R41.1, R85.2, U31.4 (VCC), U41.2 (Vout), U41.4 (Tab), U82.5 (VCC); also elsewhere on the board
+3.3VUSB: C87.1, C88.1, C89.1, L82.2, U81.4 (V3), U81.16 (VCC)
+5V: C41.1, D41.2 (K), J41.2, J52.11, U41.3 (Vin); also elsewhere on the board
+5VUSB: C83.1, J41.1, L81.2
/misc/USBE_DM: D81.6 (IO4), J81.2 (D-), T81.1
/misc/USBE_DP: D81.4 (IO3), J81.3 (D+), T81.4
/misc/USB_DM: T81.2, U81.6 (UD-)
/misc/USB_DP: T81.3, U81.5 (UD+)
/misc/XI: C84.1, U81.7 (XI), X81.1 (A)
/misc/XO: C85.1, U81.8 (XO), X81.3 (B)
ETHTXC: R83.2; also elsewhere on the board
GND: C31.2, C32.2, C41.2, C42.2, C43.2, C81.2, C82.2, C83.2, C84.2, C85.2, C86.2, C87.2, C88.2, C89.2, C90.2, D42.2 (K), D81.2 (GND), D81.3 (IO2), J51.1, J51.12, J52.1, J52.12, J81.5 (GND), J81.6 (CH), R31.1, R51.1, R52.1, R53.1, R54.1, R55.1, R56.1, S31.3, S31.4, S31.5, S31.6, U31.1 (GND), U41.1 (GND), U81.1 (GND), U82.3 (GND), X81.2 (GND), X81.4 (GND); also elsewhere on the board
GPIO2: J51.6; also elsewhere on the board
GPIO5: J51.9; also elsewhere on the board
GPIO12: J51.3; also elsewhere on the board
GPIO13: J51.4; also elsewhere on the board
GPIO14: J51.2; also elsewhere on the board
GPIO15: J51.5; also elsewhere on the board
GPIO16: J51.7; also elsewhere on the board
GPIO17: J51.8; also elsewhere on the board
GPIO34: J52.7, R51.2; also elsewhere on the board
GPIO35: J52.6, R52.2; also elsewhere on the board
GPIO36: J52.5, R53.2; also elsewhere on the board
GPIO37: J52.4, R54.2; also elsewhere on the board
GPIO38: J52.3, R55.2; also elsewhere on the board
GPIO39: J52.2, R56.2; also elsewhere on the board
unnamed: C81.1, C82.1, D81.5 (VDD), J81.1 (VCC), L81.1
unnamed: D42.1 (A), R41.2
unnamed: D81.1 (IO1), J81.4 (ID)
unnamed: D82.1 (A), R83.1
unnamed: D82.2 (K), Q81.3 (C)
unnamed: D83.1 (A), R84.1
unnamed: D83.2 (K), Q82.3 (C)
unnamed: Q81.1 (B), R81.2
unnamed: Q81.2 (E), R82.1, U81.13 (~DTR)
unnamed: Q82.1 (B), R82.2
unnamed: Q82.2 (E), R81.1, U81.14 (~RTS)
unnamed: R32.2, S31.1, S31.2
RXD0: J52.9, R85.1, U82.1 (A); also elsewhere on the board
RXD0M: U82.4 (Y); also elsewhere on the board
RXD0U: U81.2 (TXD), U82.2 (B)
TXD0: J52.8, U81.3 (RXD); also elsewhere on the board
~MR: C32.1, D31.1 (A), J51.11, R32.1, R84.2, U31.3 (~MR); also elsewhere on the board
~RESET: J51.10, R31.2, U31.2 (~RESET); also elsewhere on the board

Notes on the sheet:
Reset
USB
Mechanical
PSU
~{DTR} ~{RTS} ~{MR} ETHTXC 0 0 1 1 0 1 1 0 1 0 0 1 1 1 1 1
GPIOs
